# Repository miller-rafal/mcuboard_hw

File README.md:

### KiCad files for the ATmega16/32 microcontroller board.

The "production" folder contains all files necessary to order the board from PCBWay.

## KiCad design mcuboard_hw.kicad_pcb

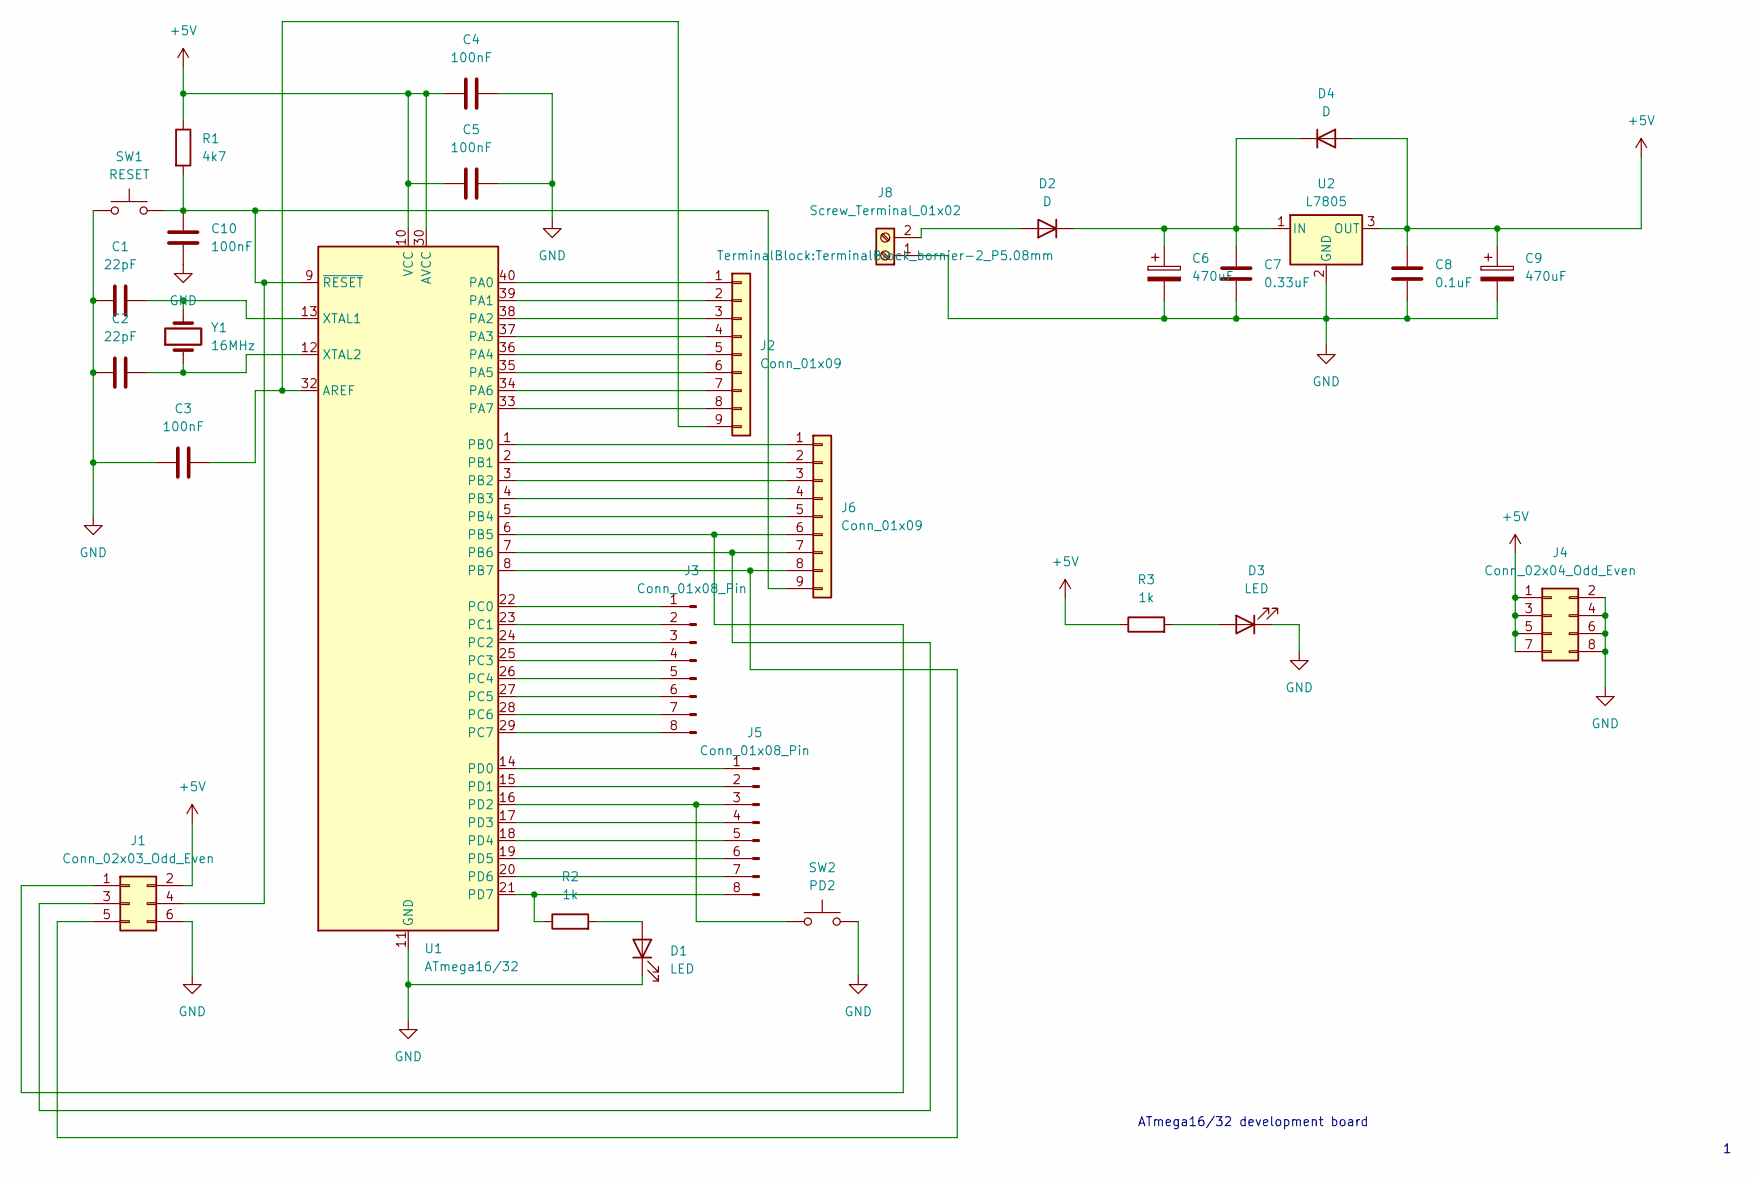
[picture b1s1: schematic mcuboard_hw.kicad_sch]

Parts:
C1, C2: 22pF; C_Disc_D6.0mm_W2.5mm_P5.00mm
C3, C4, C5, C10: 100nF; C_Disc_D6.0mm_W2.5mm_P5.00mm
C6, C9: 470uF; CP_Radial_D10.0mm_P5.00mm
C7: 0.33uF; C_Disc_D6.0mm_W2.5mm_P5.00mm
C8: 0.1uF; C_Disc_D6.0mm_W2.5mm_P5.00mm
D1, D3: LED; LED_D5.0mm
D2, D4: D; D_DO-41_SOD81_P7.62mm_Horizontal
J1: Conn_02x03_Odd_Even; PinHeader_2x03_P2.54mm_Vertical
J2, J6: Conn_01x09; PinHeader_1x09_P2.54mm_Vertical
J3, J5: Conn_01x08_Pin; PinHeader_1x08_P2.54mm_Vertical
J4: Conn_02x04_Odd_Even; PinHeader_2x04_P2.54mm_Vertical
J8: Screw_Terminal_01x02; TerminalBlock_bornier-2_P5.08mm
R1: 4k7; R_Axial_DIN0207_L6.3mm_D2.5mm_P10.16mm_Horizontal
R2, R3: 1k; R_Axial_DIN0207_L6.3mm_D2.5mm_P10.16mm_Horizontal
SW1: RESET; SW_PUSH_6mm
SW2: PD2; SW_PUSH_6mm
U1: ATmega16/32; DIP-40_W15.24mm
U2: L7805; TO-220-3_Vertical
Y1: 16MHz; Crystal_HC49-U_Vertical

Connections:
+5V: C4.2, C5.2, C8.1, C9.1, D4.2 (A), J1.2, J4.1, J4.3, J4.5, J4.7, R1.1, R3.1, U1.10 (VCC), U1.30 (AVCC), U2.3 (OUT)
GND: C1.2, C2.2, C3.2, C4.1, C5.1, C6.2, C7.2, C8.2, C9.2, C10.2, D1.1 (K), D3.1 (K), J1.6, J4.2, J4.4, J4.6, J4.8, J8.1, SW1.1, SW2.2, U1.11 (GND), U1.31 (GND), U2.2 (GND)
unnamed: D1.2 (A), R2.2
unnamed: D2.2 (A), J8.2
unnamed: C6.1, C7.1, D2.1 (K), D4.1 (K), U2.1 (IN)
unnamed: D3.2 (A), R3.2
unnamed: J1.1, J6.6, U1.6 (PB5)
unnamed: J1.3, J6.7, U1.7 (PB6)
unnamed: C10.1, J1.4, J6.9, R1.2, SW1.2, U1.9 (~RESET)
unnamed: J1.5, J6.8, U1.8 (PB7)
unnamed: J2.1, U1.40 (PA0)
unnamed: J2.2, U1.39 (PA1)
unnamed: J2.3, U1.38 (PA2)
unnamed: J2.4, U1.37 (PA3)
unnamed: J2.5, U1.36 (PA4)
unnamed: J2.6, U1.35 (PA5)
unnamed: J2.7, U1.34 (PA6)
unnamed: J2.8, U1.33 (PA7)
unnamed: C3.1, J2.9, U1.32 (AREF)
unnamed: J3.1, U1.22 (PC0)
unnamed: J3.2, U1.23 (PC1)
unnamed: J3.3, U1.24 (PC2)
unnamed: J3.4, U1.25 (PC3)
unnamed: J3.5, U1.26 (PC4)
unnamed: J3.6, U1.27 (PC5)
unnamed: J3.7, U1.28 (PC6)
unnamed: J3.8, U1.29 (PC7)
unnamed: J5.1, U1.14 (PD0)
unnamed: J5.2, U1.15 (PD1)
unnamed: J5.3, SW2.1, U1.16 (PD2)
unnamed: J5.4, U1.17 (PD3)
unnamed: J5.5, U1.18 (PD4)
unnamed: J5.6, U1.19 (PD5)
unnamed: J5.7, U1.20 (PD6)
unnamed: J5.8, R2.1, U1.21 (PD7)
unnamed: J6.1, U1.1 (PB0)
unnamed: J6.2, U1.2 (PB1)
unnamed: J6.3, U1.3 (PB2)
unnamed: J6.4, U1.4 (PB3)
unnamed: J6.5, U1.5 (PB4)
unnamed: C1.1, U1.13 (XTAL1), Y1.2
unnamed: C2.1, U1.12 (XTAL2), Y1.1

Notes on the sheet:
ATmega16/32 development board

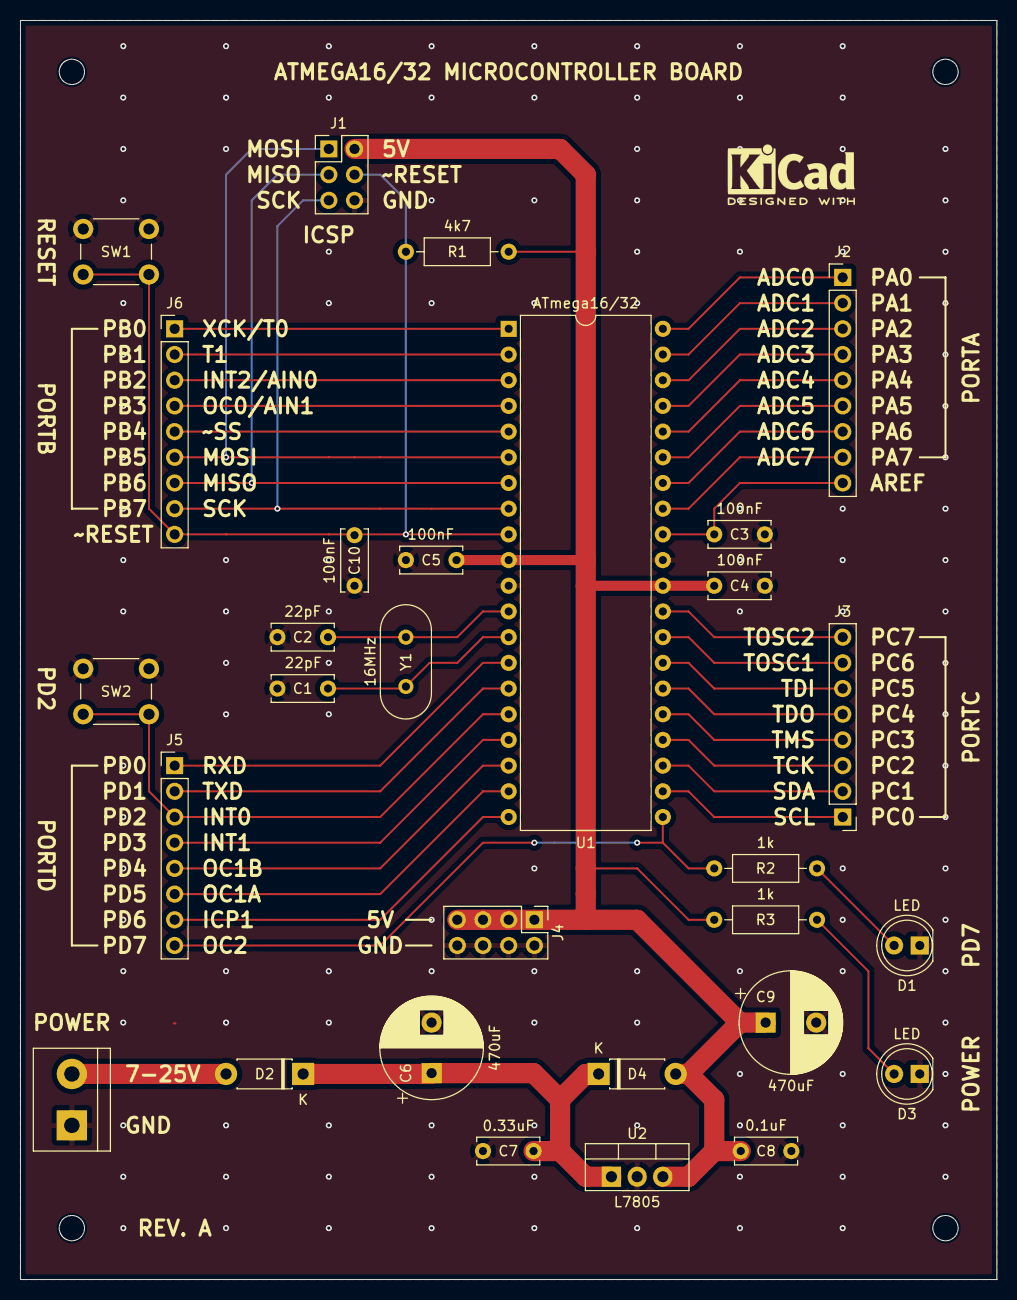
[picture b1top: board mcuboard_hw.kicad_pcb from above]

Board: 2 copper layers, 96.5 x 124.5 mm, 29 parts (0 on the bottom side), 42 nets.
